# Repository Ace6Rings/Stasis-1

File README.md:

# OVERVIEW

The Reshular Robot Arm is a 6 DOF robotic arm. It is operated over bluetooth so it can be operated remotely.
5 stepper motors, using the TMC2209 driver, and 1 servo motor is used to make this huge robotic arm.

# Purpose

I made this because I've always been fascinated on how to use technology to make an impact on the physical world. 
I've seen small robotic arms powered with servo motors. But I noticed that scaling it up in size changes the materials I need 
and introduces (newish) problems like insufficient torque when using a servo motor. These robotic arms are also shorter ranged and can only hold
very light and small items. Thats why I built this robotic arm. I can lift items that are impossible for small robotic arms like a big book. 
The most important thing is that I became way better at eda since this is my first project that uses a smd PCB.

# Schematic

There are 5 tmc 2209 motor drivers. They are almost identical. Only their gpio assignments to dir and step changes and also their uart configuration.

So how did I configure it and how can you too?

The tmc2209 talks to the esp32 via UART. But four tmc 2209s share one uart line. Wait, there's 5 tmcs, not 4! How could that be?
Well, the ID for uart is dictated by the whether your ms1 and ms2 are pulled high or low. Since there are 2 states and 2 pins, 2^2 is 4. So you get 4 combinations.
To account for the 5th tmc 2209, I just used another set of gpios.

The ms1 and ms2 pins also happen to control microstepping, and thats pretty important if you have something like an EV or a robot arm like this. So I put the finer microstepping onto parts that actually matter, such as the elbow joint. You can find further details via the datasheet for the TMC2209 and the exact configuration in the PCB file that I have.
# PCB

Now lets get into the PCB.
The specs of the PCB isn't anything special. It is a 2 layer pcb, and thats exactly why this is good. It's theoretically not gonna perform as well as a four layer board (well not really because this is a 2 layer board thing). But since its only 2 layers, the cost decreases significantly. There are two layers of electrical protection. The first one is the NCP1117 (well not really? but if it dies the circuit becomes open so I guess it is protection), and the second one is the TVS diode. The TVS diode is a component that protects your circuit when the voltage/current reaches a certain threshold. For something like a robot arm, you will defininately one that.
# Model
The purpose of the model is not to make it look good but to make it as light as possible to test in real life. 
It features 6 degrees of freedom, which could move (almost) ny item in any way you could think of.

The base has an hexagonal pattern which maximizes strength, aesthetics, and filament efficiency.
# Motor joints

Well, how does each joint work? Its actually quite simple. You can tell by the picture that the stepper motors are directly attached to each joint, so no special pullys or anything! This saves complexity and cost. For the gripper, its a little different.

The central gear meshes with the two side parts. When it spins, the two grippers come together and, well, grips. Spinning it the opposite way retracts it. You can try it out in this link.
https://cad.onshape.com/documents/dfb7d85a38278a669fcebbb5/w/2d92252d034fc83197e6695c/e/ec9dc79179103d4b89a939a4?renderMode=0&uiState=6a322868ee269b265a1ceec7

As you can see, the motor is directly attached.

# Testing

N/A (will include after getting parts)

# Bill of Materials

| Name                          | Purpose                            | Quantity | Total Cost (USD) | Link                                                                                                                                                                                         | Distributor |
|-------------------------------|------------------------------------|----------|------------------|----------------------------------------------------------------------------------------------------------------------------------------------------------------------------------------------|-------------|
| li ion batteries              | batteries to power my robot arm    | 1        | 25.98            | https://www.amazon.com/Mupoer-Rechargeable-Batteries-Integrated-Charging/dp/B0D4M581B3/ref=sr_1_15?sr=8-15                                                                                   | amazon      |
| ds3225                        | gripper motor                      | 1        | 16.99            | https://www.amazon.com/gp/product/B0CNTG877G/ref=ox_sc_act_title_1?smid=A1PKC2PUMNR8VD                                                                                                       | amazon      |
| HEAT SET INSERTS              | To assemble my robot arm           | 1        | 9.98             | https://www.amazon.com/M2-M2-5-M3-Threaded-Inserts/dp/B0FH4JQ3VB/ref=sr_1_4?sr=8-4                                                                                                           | amazon      |
| 175-TMC2209-LA-TCT-ND         | IC MTR DRV 4.75-28V QFN28          | 10       | 40.89            | https://www.digikey.com/en/products/detail/analog-devices-inc-maxim-integrated/TMC2209-LA-T/10232491                                                                                         | DIGIKEY     |
| NCP1117LPST33T3GOSCT-ND       | IC REG LINEAR 3.3V 1A SOT-223      | 10       | 2.62             | https://www.digikey.com/en/products/detail/onsemi/NCP1117LPST33T3G/1967376                                                                                                                   | DIGIKEY     |
| 296-50511-1-ND                | UNIDIR PRECISION SURGE DIODE       | 10       | 7.06             | https://www.digikey.com/en/products/detail/texas-instruments/TVS1400DRVR/11589096                                                                                                            | DIGIKEY     |
| 2073-USB4085-GF-ACT-ND        | CONN RCPT USB2.0 TYPE C 16+8POS    | 2        | 2.15             | https://www.digikey.com/en/products/detail/gct/USB4085-GF-A/9859704                                                                                                                          | DIGIKEY     |
| CKN10285CT-ND                 | SWITCH TACTILE SPST-NO 0.05A 32V   | 10       | 5.81             | https://www.digikey.com/en/products/detail/c-k/KMR241NG-ULC-LFS/2747141                                                                                                                      | DIGIKEY     |
| 490-10700-1-ND                | CAP CER 0.1UF 50V X7R 0402         | 50       | 0.81             | https://www.digikey.com/en/products/detail/murata-electronics/GRM155R71H104KE14D/4358653                                                                                                     | DIGIKEY     |
| 277-1722-ND                   | TERM BLK 3POS SIDE ENT 3.5MM PCB   | 1        | 2.10             | https://www.digikey.com/en/products/detail/phoenix-contact/1984620/950937                                                                                                                    | DIGIKEY     |
| 1276-1096-1-ND                | CAP CER 10UF 16V X5R 0805          | 10       | 0.54             | https://www.digikey.com/en/products/detail/samsung-electro-mechanics/CL21A106KOQNNNE/3886902                                                                                                 | DIGIKEY     |
| 273-KDV12DR100ETCT-ND         | RES 0.1 OHM 0.5% 1/2W 1206         | 25       | 3.00             | https://www.digikey.com/en/products/detail/ohmite/KDV12DR100ET/13691867                                                                                                                      | DIGIKEY     |
| 311-5.10KLRCT-ND              | RES 5.1K OHM 1% 1/16W 0402         | 25       | 0.37             | https://www.digikey.com/en/products/detail/yageo/RC0402FR-075K1L/726633                                                                                                                      | DIGIKEY     |
| 541-10.0KLCT-ND               | RES 10K OHM 1% 1/16W 0402          | 25       | 0.59             | https://www.digikey.com/en/products/detail/vishay-dale/CRCW040210K0FKED/1176095                                                                                                              | DIGIKEY     |
| 311-100KLRCT-ND               | RES 100K OHM 1% 1/16W 0402         | 25       | 0.37             | https://www.digikey.com/en/products/detail/yageo/RC0402FR-07100KL/726651                                                                                                                     | DIGIKEY     |
| 311-1.00KLRCT-ND              | RES 1K OHM 1% 1/16W 0402           | 25       | 0.37             | https://www.digikey.com/en/products/detail/yageo/RC0402FR-071KL/726544                                                                                                                       | DIGIKEY     |
| 277-1721-ND                   | TERM BLK 2POS SIDE ENT 3.5MM PCB   | 1        | 1.46             | https://www.digikey.com/en/products/detail/phoenix-contact/1984617/950934                                                                                                                    | DIGIKEY     |
| 490-4763-1-ND                 | CAP CER 0.022UF 50V X7R 0402       | 50       | 1.01             | https://www.digikey.com/en/products/detail/murata-electronics/GCM155R71H223KA55D/2756835                                                                                                     | DIGIKEY     |
| 277-1860-ND                   | TERM BLK 4POS SIDE ENT 3.5MM PCB   | 5        | 13.45            | https://www.digikey.com/en/products/detail/phoenix-contact/1984633/950950                                                                                                                    | DIGIKEY     |
| 1965-ESP32-S3-WROOM-1-N4CT-ND | RF TXRX MODULE BT PCB TRACE SMD    | 2        | 11.46            | https://www.digikey.com/en/products/detail/espressif-systems/ESP32-S3-WROOM-1-N4/16162639                                                                                                    | DIGIKEY     |
| JLCPCB                        | To put my components on            | 1        | 36.48            | https://trade.jlcpcb.com/checkout/payMethod?systemType=order_pcb&calType=PAY&batchNum=W2026042809527003&spm=Jlcpcb.Confirmorder.1001                                                         | jlcpcb      |
| NEMA 17 motor thin            | For the arms                       | 5        | 17.50            | https://www.alibaba.com/product-detail/Special-Offer-26mm-Length-NEMA-17_1601043669710.html?spm=a2700.prosearch.normal_offer.d_title.659167afAhymea&priceId=58dcbf79d3ef4e1099ae55c89d924238 | Alibaba     |
| M2-M5 assortment screws       | To screw pcb, battery holders, and | 1        | 12.38            | https://www.amazon.com/Countersunk-Assortment-Phillips-Machine-Washers/dp/B0F87JTJ6T/ref=sr_1_3?sr=8-3                                                                                       | Amazon      |
| mr105                         | bearings for high torque load      | 4        | 8.79             | https://www.amazon.com/MR105-2RS-Deep-Groove-Ball-Bearings/dp/B0DXZNSMJC/ref=sr_1_6?sr=8-6                                                                                                   | amazon      |

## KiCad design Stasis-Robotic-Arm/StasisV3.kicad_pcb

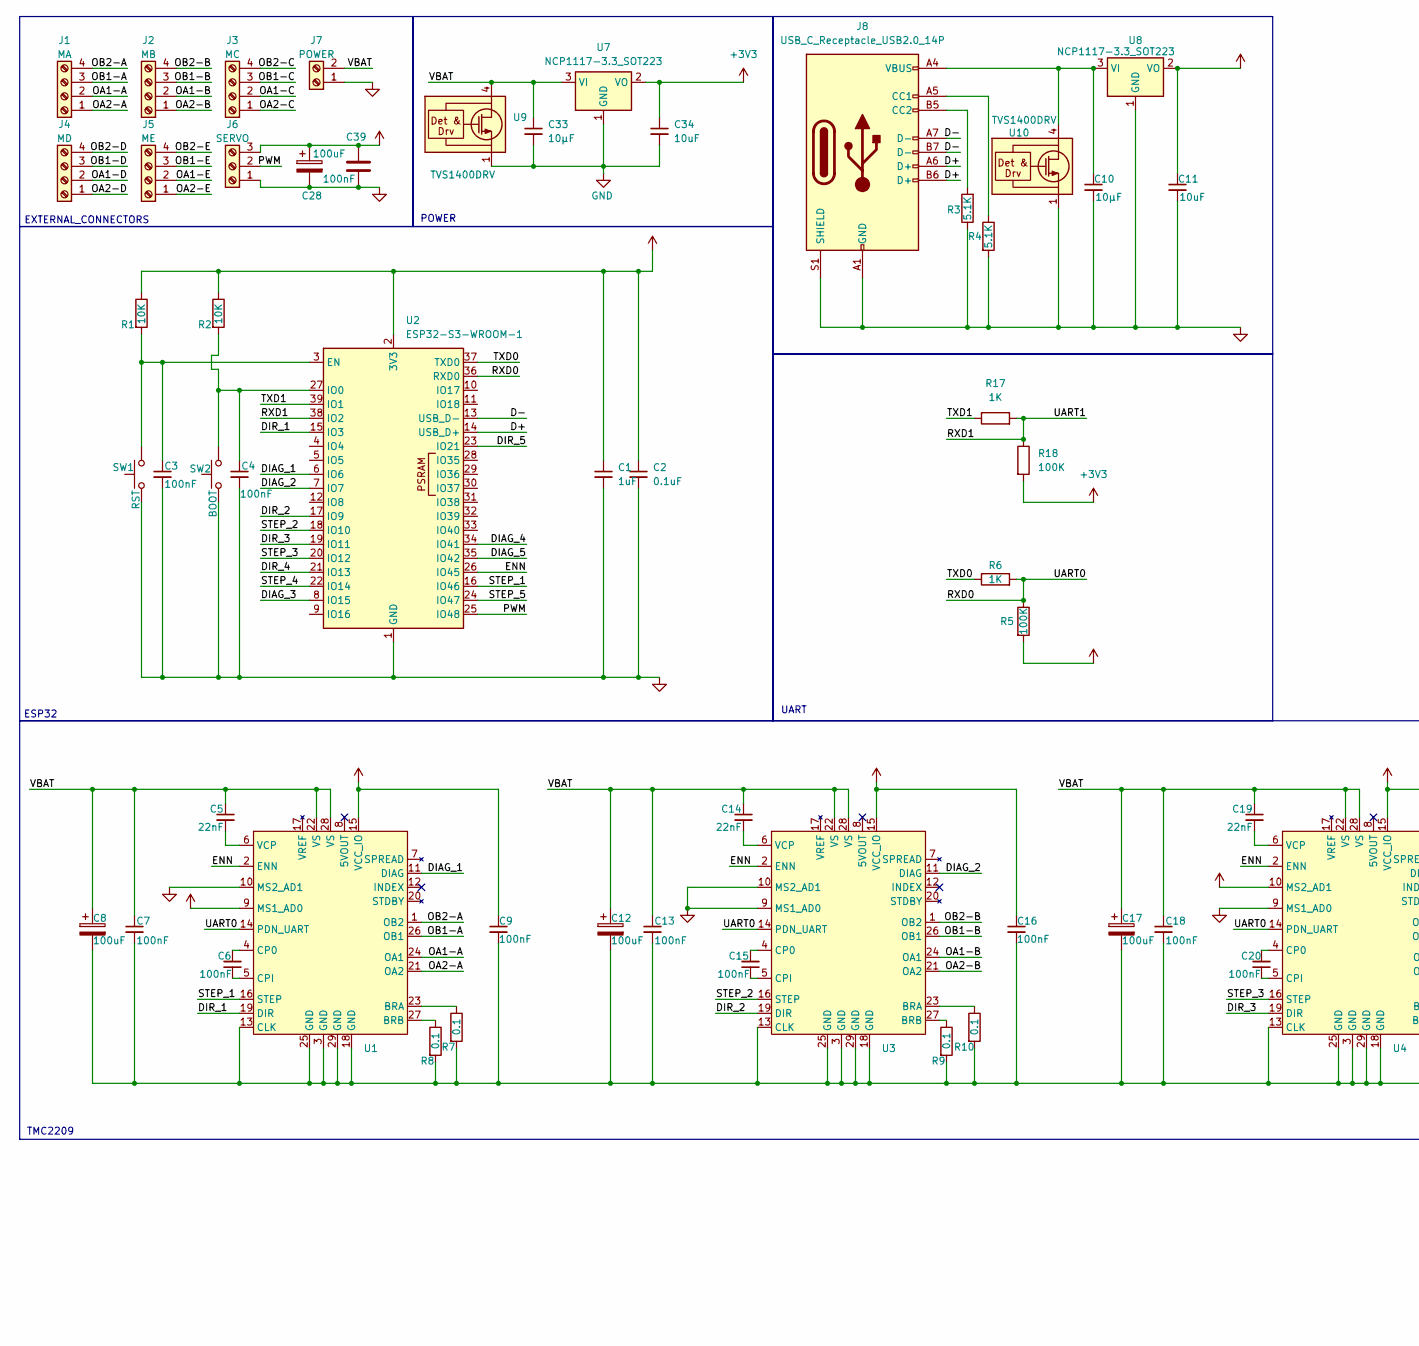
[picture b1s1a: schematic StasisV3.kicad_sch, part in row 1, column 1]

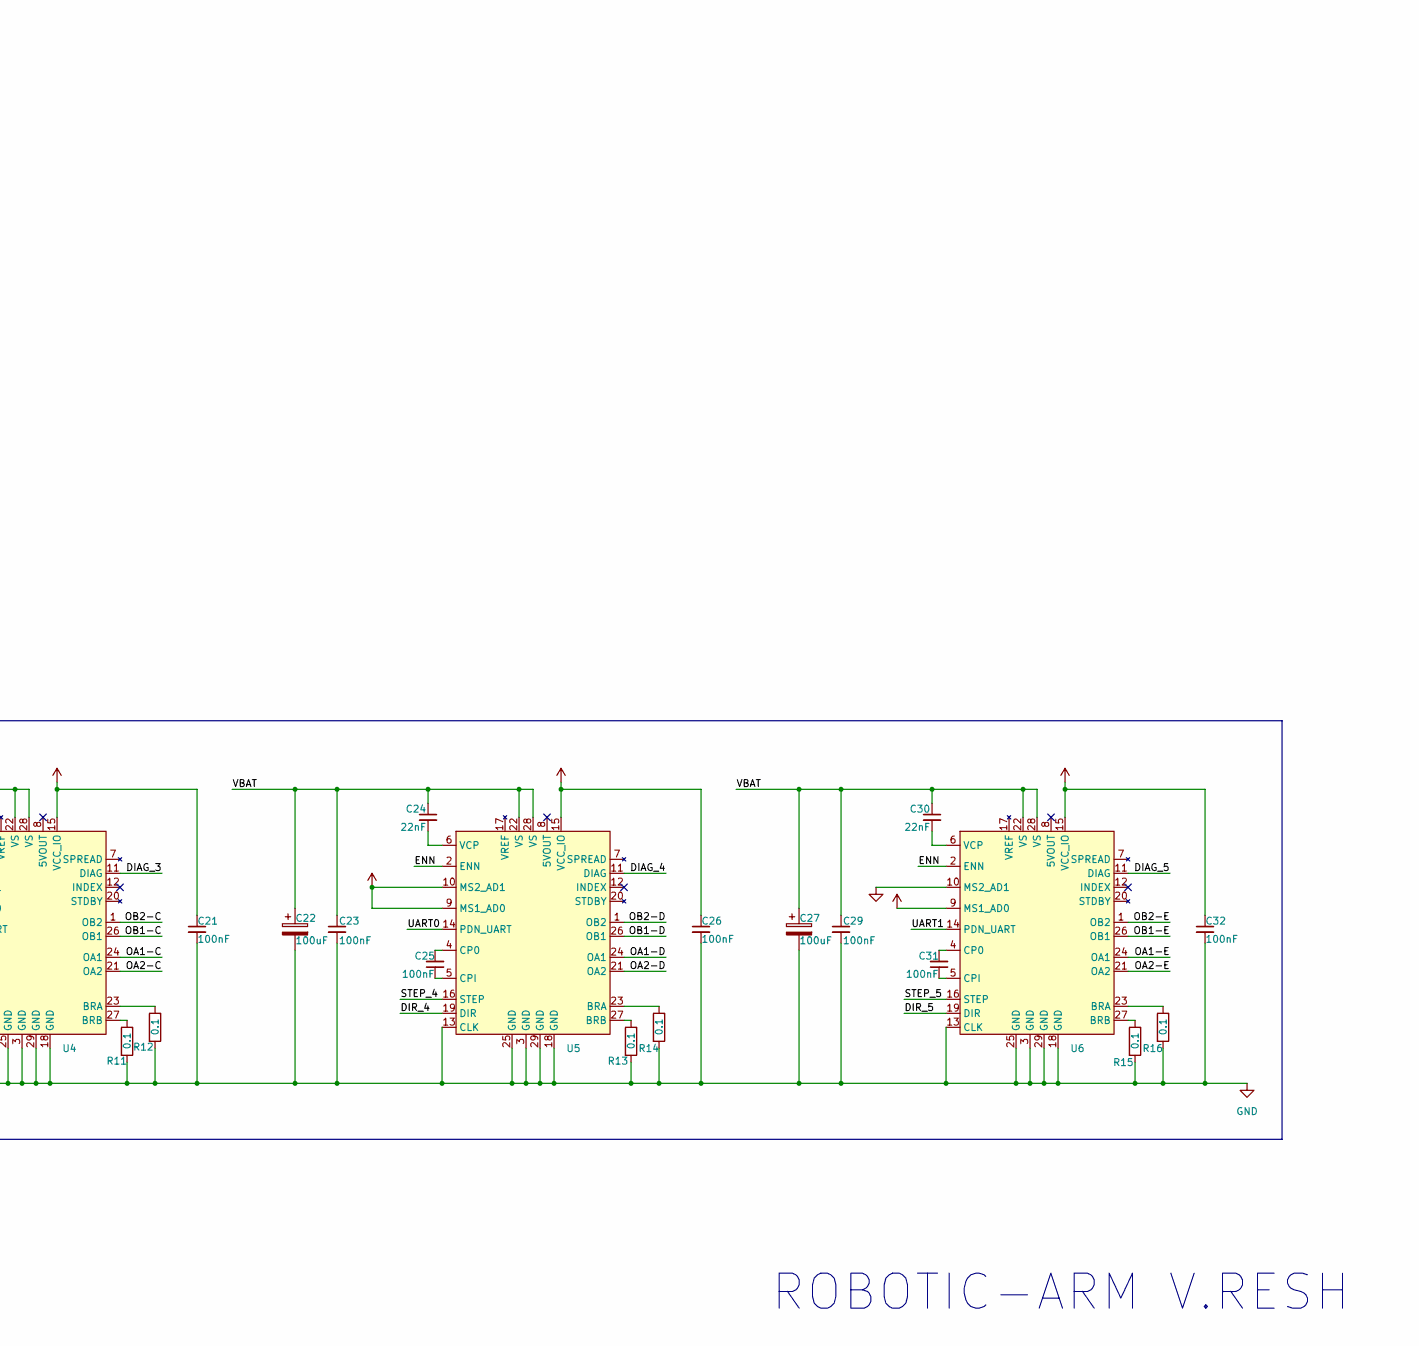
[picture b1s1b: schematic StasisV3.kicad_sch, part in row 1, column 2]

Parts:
C1: 1uF; C_0402_1005Metric
C2: 0.1uF; C_0402_1005Metric
C3, C4, C6, C7, C9, C13, C15, C16, C18, C20, C21, C23, C25, C26, C29, C31, C32, C39: 100nF; C_0402_1005Metric
C5, C14, C19, C24, C30: 22nF; C_0402_1005Metric
C8, C12, C17, C22, C27, C28: 100uF; CP_EIA-6032-28_Kemet-C
C10, C33: 10μF; C_0805_2012Metric
C11, C34: 10uF; C_0805_2012Metric
J1: MA; TerminalBlock_Phoenix_PT-1,5-4-3.5-H_1x04_P3.50mm_Horizontal
J2: MB; TerminalBlock_Phoenix_PT-1,5-4-3.5-H_1x04_P3.50mm_Horizontal
J3: MC; TerminalBlock_Phoenix_PT-1,5-4-3.5-H_1x04_P3.50mm_Horizontal
J4: MD; TerminalBlock_Phoenix_PT-1,5-4-3.5-H_1x04_P3.50mm_Horizontal
J5: ME; TerminalBlock_Phoenix_PT-1,5-4-3.5-H_1x04_P3.50mm_Horizontal
J6: SERVO; TerminalBlock_Phoenix_PT-1,5-3-3.5-H_1x03_P3.50mm_Horizontal
J7: POWER; TerminalBlock_Phoenix_PT-1,5-2-3.5-H_1x02_P3.50mm_Horizontal
J8: USB_C_Receptacle_USB2.0_14P; USB_C_Receptacle_GCT_USB4105-xx-A_16P_TopMnt_Horizontal
R1, R2: 10K; R_0402_1005Metric
R3, R4: 5.1K; R_0402_1005Metric
R5, R18: 100K; R_0402_1005Metric
R6, R17: 1K; R_0402_1005Metric
R7, R8, R9, R10, R11, R12, R13, R14, R15, R16: 0.1; R_1206_3216Metric
SW1: RST; SW_Push_1P1T_NO_CK_KMR2
SW2: BOOT; SW_Push_1P1T_NO_CK_KMR2
U1, U3, U4, U5, U6: tmc2209
U2: ESP32-S3-WROOM-1
U7, U8: NCP1117-3.3_SOT223; SOT-223-3_TabPin2
U9, U10: TVS1400DRV; WSON-6-1EP_2x2mm_P0.65mm_EP1x1.6mm

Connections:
+3V3: C1.1, C2.1, C9.1, C11.1, C16.1, C21.1, C26.1, C32.1, C34.1, R1.1, R2.1, R5.2, R18.2, U1.9 (MS1_AD0), U1.15 (VCC_IO), U2.2 (3V3), U3.15 (VCC_IO), U4.10 (MS2_AD1), U4.15 (VCC_IO), U5.9 (MS1_AD0), U5.10 (MS2_AD1), U5.15 (VCC_IO), U6.9 (MS1_AD0), U6.15 (VCC_IO), U7.2 (VO), U8.2 (VO)
/D+: J8.A6 (D+), J8.B6 (D+), U2.14 (USB_D+)
/D-: J8.A7 (D-), J8.B7 (D-), U2.13 (USB_D-)
/DIAG_1: U1.11 (DIAG), U2.6 (IO6)
/DIAG_2: U2.7 (IO7), U3.11 (DIAG)
/DIAG_3: U2.8 (IO15), U4.11 (DIAG)
/DIAG_4: U2.34 (IO41), U5.11 (DIAG)
/DIAG_5: U2.35 (IO42), U6.11 (DIAG)
/DIR_1: U1.19 (DIR), U2.15 (IO3)
/DIR_2: U2.17 (IO9), U3.19 (DIR)
/DIR_3: U2.19 (IO11), U4.19 (DIR)
/DIR_4: U2.21 (IO13), U5.19 (DIR)
/DIR_5: U2.23 (IO21), U6.19 (DIR)
/ENN: U1.2 (ENN), U2.26 (IO45), U3.2 (ENN), U4.2 (ENN), U5.2 (ENN), U6.2 (ENN)
/OA1-A: J1.2, U1.24 (OA1)
/OA1-B: J2.2, U3.24 (OA1)
/OA1-C: J3.2, U4.24 (OA1)
/OA1-D: J4.2, U5.24 (OA1)
/OA1-E: J5.2, U6.24 (OA1)
/OA2-A: J1.1, U1.21 (OA2)
/OA2-B: J2.1, U3.21 (OA2)
/OA2-C: J3.1, U4.21 (OA2)
/OA2-D: J4.1, U5.21 (OA2)
/OA2-E: J5.1, U6.21 (OA2)
/OB1-A: J1.3, U1.26 (OB1)
/OB1-B: J2.3, U3.26 (OB1)
/OB1-C: J3.3, U4.26 (OB1)
/OB1-D: J4.3, U5.26 (OB1)
/OB1-E: J5.3, U6.26 (OB1)
/OB2-A: J1.4, U1.1 (OB2)
/OB2-B: J2.4, U3.1 (OB2)
/OB2-C: J3.4, U4.1 (OB2)
/OB2-D: J4.4, U5.1 (OB2)
/OB2-E: J5.4, U6.1 (OB2)
/PWM: J6.2, U2.25 (IO48)
/RXD0: R5.1, R6.2, U1.14 (PDN_UART), U2.36 (RXD0), U3.14 (PDN_UART), U4.14 (PDN_UART), U5.14 (PDN_UART)
/RXD1: R17.2, R18.1, U2.38 (IO2), U6.14 (PDN_UART)
/STEP_1: U1.16 (STEP), U2.16 (IO46)
/STEP_2: U2.18 (IO10), U3.16 (STEP)
/STEP_3: U2.20 (IO12), U4.16 (STEP)
/STEP_4: U2.22 (IO14), U5.16 (STEP)
/STEP_5: U2.24 (IO47), U6.16 (STEP)
/TXD0: R6.1, U2.37 (TXD0)
/TXD1: R17.1, U2.39 (IO1)
unnamed: J8.A5 (CC1), R4.1
unnamed: J8.B5 (CC2), R3.2
unnamed: R7.1, U1.23 (BRA)
unnamed: R8.1, U1.27 (BRB)
unnamed: C6.2, U1.4 (CP0)
unnamed: C6.1, U1.5 (CPI)
unnamed: C5.2, U1.6 (VCP)
unnamed: R10.1, U3.23 (BRA)
unnamed: R9.1, U3.27 (BRB)
unnamed: C15.2, U3.4 (CP0)
unnamed: C15.1, U3.5 (CPI)
unnamed: C14.2, U3.6 (VCP)
unnamed: R12.1, U4.23 (BRA)
unnamed: R11.1, U4.27 (BRB)
unnamed: C20.2, U4.4 (CP0)
unnamed: C20.1, U4.5 (CPI)
unnamed: C19.2, U4.6 (VCP)
unnamed: R14.1, U5.23 (BRA)
unnamed: R13.1, U5.27 (BRB)
unnamed: C25.2, U5.4 (CP0)
unnamed: C25.1, U5.5 (CPI)
unnamed: C24.2, U5.6 (VCP)
unnamed: R16.1, U6.23 (BRA)
unnamed: R15.1, U6.27 (BRB)
unnamed: C31.2, U6.4 (CP0)
unnamed: C31.1, U6.5 (CPI)
unnamed: C30.2, U6.6 (VCP)
unnamed: C10.1, J8.A4 (VBUS), J8.A9 (VBUS), J8.B4 (VBUS), J8.B9 (VBUS), U8.3 (VI), U10.4 (IN), U10.5 (IN), U10.6 (IN)
VBAT: C5.1, C7.1, C8.1, C12.1, C13.1, C14.1, C17.1, C18.1, C19.1, C22.1, C23.1, C24.1, C27.1, C28.1, C29.1, C30.1, C33.1, C39.2, J6.3, J7.2, U1.22 (VS), U1.28 (VS), U3.22 (VS), U3.28 (VS), U4.22 (VS), U4.28 (VS), U5.22 (VS), U5.28 (VS), U6.22 (VS), U6.28 (VS), U7.3 (VI), U9.4 (IN), U9.5 (IN), U9.6 (IN)

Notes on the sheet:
TMC2209
POWER
UART
ESP32
EXTERNAL_CONNECTORS
ROBOTIC-ARM V.RESH

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
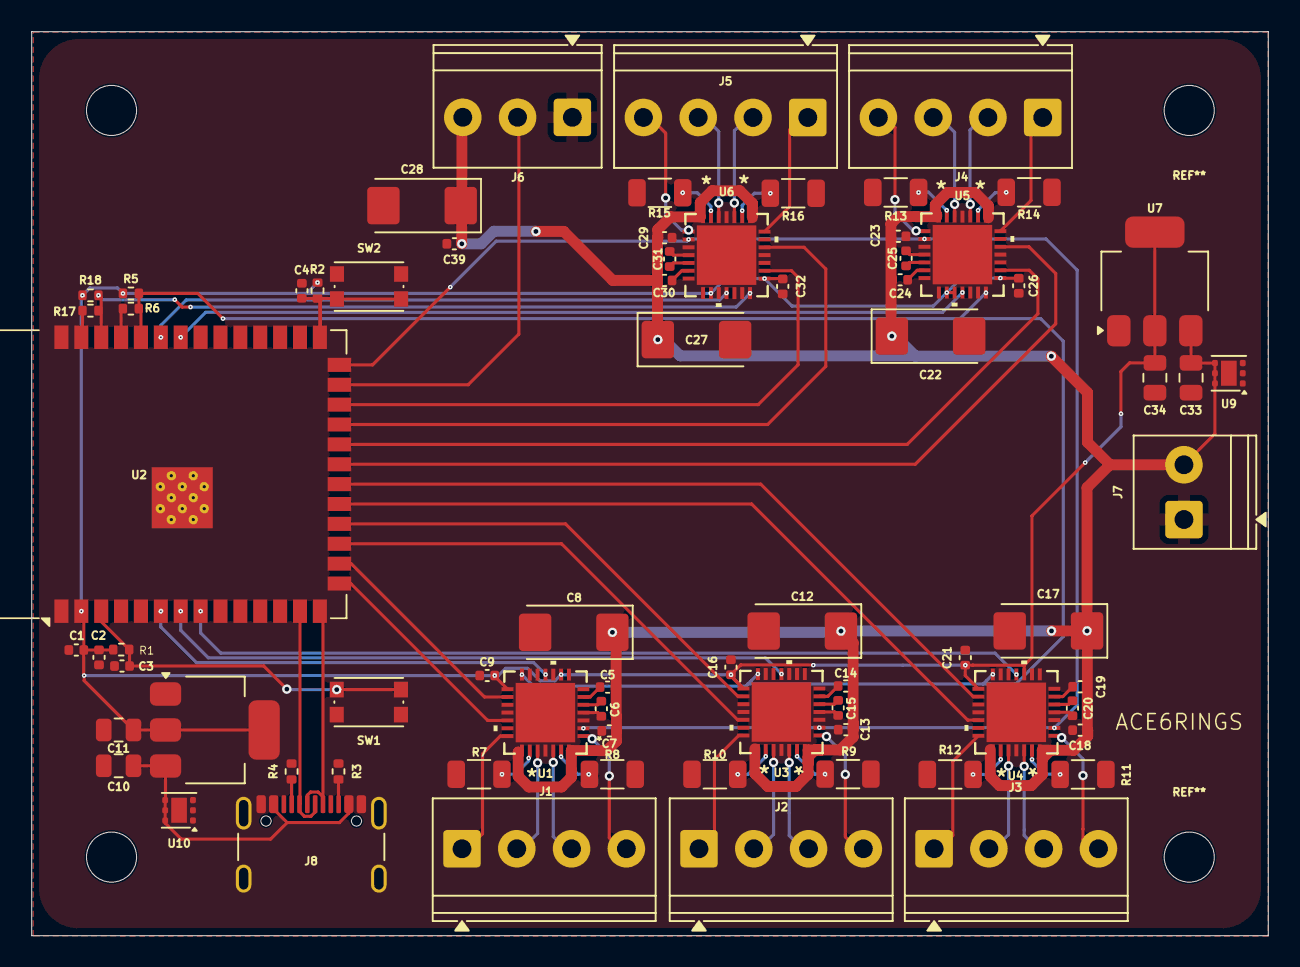
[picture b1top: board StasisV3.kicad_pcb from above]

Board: 2 copper layers, 79.0 x 57.8 mm, 73 parts (0 on the bottom side), 76 nets.

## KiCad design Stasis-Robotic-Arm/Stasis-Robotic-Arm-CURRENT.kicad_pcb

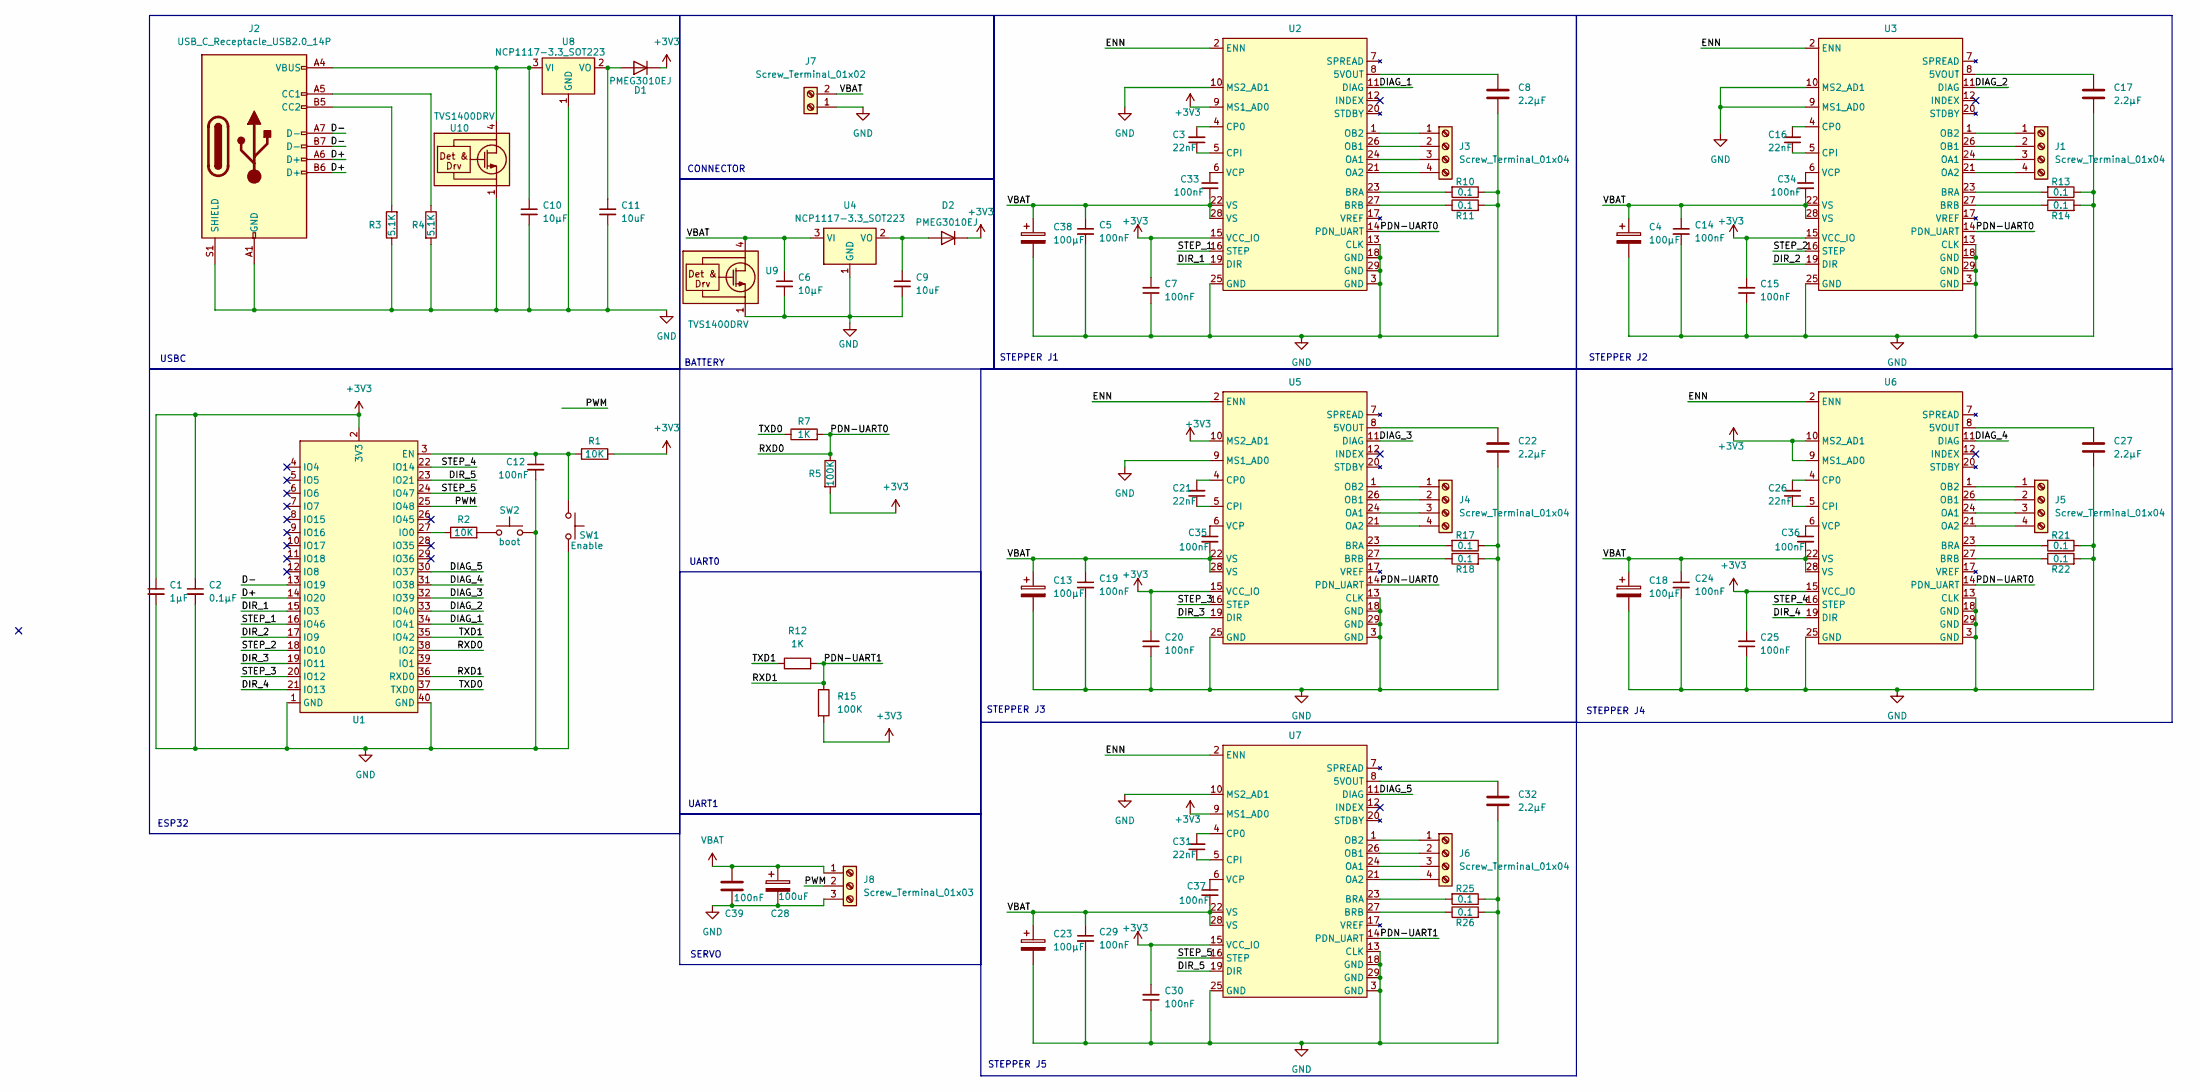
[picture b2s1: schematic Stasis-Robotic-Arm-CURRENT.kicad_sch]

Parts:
C1: 1μF; C_0402_1005Metric
C2: 0.1μF; C_0402_1005Metric
C3, C16, C21, C26, C31: 22nF; C_0402_1005Metric
C4, C13, C18, C23, C38: 100μF; CP_EIA-6032-28_Kemet-C
C5, C7, C12, C14, C15, C19, C20, C24, C25, C29, C30, C33, C34, C35, C36, C37, C39: 100nF; C_0402_1005Metric
C6, C10: 10μF; C_0805_2012Metric
C8, C17, C22, C27, C32: 2.2μF; C_0603_1608Metric
C9, C11: 10uF; C_0805_2012Metric
C28: 100uF; CP_EIA-6032-28_Kemet-C
D1, D2: PMEG3010EJ; D_SOD-123
J1, J3, J4, J5, J6: Screw_Terminal_01x04; PhoenixContact_GMSTBVA_2,5_4-G-7,62_1x04_P7.62mm_Vertical
J2: USB_C_Receptacle_USB2.0_14P; USB_C_Receptacle_GCT_USB4105-xx-A_16P_TopMnt_Horizontal
J7: Screw_Terminal_01x02; PhoenixContact_GMSTBVA_2,5_2-G-7,62_1x02_P7.62mm_Vertical
J8: Screw_Terminal_01x03; PhoenixContact_GMSTBVA_2,5_3-G-7,62_1x03_P7.62mm_Vertical
R1, R2: 10K; R_0402_1005Metric
R3, R4: 5.1K; R_0402_1005Metric
R5, R15: 100K; R_0402_1005Metric
R7, R12: 1K; R_0402_1005Metric
R10, R11, R13, R14, R17, R18, R21, R22, R25, R26: 0.1; R_1206_3216Metric
SW1: Enable; SW_Push_1P1T_NO_CK_KMR2
SW2: boot; SW_Push_1P1T_NO_CK_KMR2
U1: ESP32-S3-WROOM-1
U2, U3, U5, U6, U7: tmc2209
U4, U8: NCP1117-3.3_SOT223; SOT-223-3_TabPin2
U9, U10: TVS1400DRV; WSON-6-1EP_2x2mm_P0.65mm_EP1x1.6mm

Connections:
+3V3: C1.1, C2.1, C7.2, C15.2, C20.2, C25.2, C30.2, D1.1 (K), D2.1 (K), R1.2, R5.2, R15.2, U1.2 (3V3), U2.9 (MS1_AD0), U2.15 (VCC_IO), U3.15 (VCC_IO), U5.10 (MS2_AD1), U5.15 (VCC_IO), U6.9 (MS1_AD0), U6.10 (MS2_AD1), U6.15 (VCC_IO), U7.9 (MS1_AD0), U7.15 (VCC_IO)
/D+: J2.A6 (D+), J2.B6 (D+), U1.14 (IO20)
/D-: J2.A7 (D-), J2.B7 (D-), U1.13 (IO19)
/DIAG_1: U1.34 (IO41), U2.11 (DIAG)
/DIAG_2: U1.33 (IO40), U3.11 (DIAG)
/DIAG_3: U1.32 (IO39), U5.11 (DIAG)
/DIAG_4: U1.31 (IO38), U6.11 (DIAG)
/DIAG_5: U1.30 (IO37), U7.11 (DIAG)
/DIR_1: U1.15 (IO3), U2.19 (DIR)
/DIR_2: U1.17 (IO9), U3.19 (DIR)
/DIR_3: U1.19 (IO11), U5.19 (DIR)
/DIR_4: U1.21 (IO13), U6.19 (DIR)
/DIR_5: U1.23 (IO21), U7.19 (DIR)
/ENN: U2.2 (ENN), U3.2 (ENN), U5.2 (ENN), U6.2 (ENN), U7.2 (ENN)
/PDN-UART0: R5.1, R7.2, U1.38 (IO2), U2.14 (PDN_UART), U3.14 (PDN_UART), U5.14 (PDN_UART), U6.14 (PDN_UART)
/PDN-UART1: R12.2, R15.1, U1.36 (RXD0), U7.14 (PDN_UART)
/PWM: J8.2, U1.25 (IO48)
/STEP_1: U1.16 (IO46), U2.16 (STEP)
/STEP_2: U1.18 (IO10), U3.16 (STEP)
/STEP_3: U1.20 (IO12), U5.16 (STEP)
/STEP_4: U1.22 (IO14), U6.16 (STEP)
/STEP_5: U1.24 (IO47), U7.16 (STEP)
/TXD0: R7.1, U1.37 (TXD0)
/TXD1: R12.1, U1.35 (IO42)
GND: C1.2, C2.2, C4.2, C5.2, C6.2, C7.1, C8.2, C9.2, C10.2, C11.2, C12.2, C13.2, C14.2, C15.1, C17.2, C18.2, C19.2, C20.1, C22.2, C23.2, C24.2, C25.1, C27.2, C28.2, C29.2, C30.1, C32.2, C38.2, C39.2, J2.A1 (GND), J2.A12 (GND), J2.B1 (GND), J2.B12 (GND), J2.S1 (SHIELD), J7.1, J8.3, R3.1, R4.2, R10.1, R11.2, R13.1, R14.2, R17.1, R18.2, R21.1, R22.2, R25.1, R26.2, SW1.1, SW2.2, U1.1 (GND), U1.40 (GND), U2.3 (GND), U2.10 (MS2_AD1), U2.13 (CLK), U2.18 (GND), U2.25 (GND), U2.29 (GND), U3.3 (GND), U3.9 (MS1_AD0), U3.10 (MS2_AD1), U3.13 (CLK), U3.18 (GND), U3.25 (GND), U3.29 (GND), U4.1 (GND), U5.3 (GND), U5.9 (MS1_AD0), U5.13 (CLK), U5.18 (GND), U5.25 (GND), U5.29 (GND), U6.3 (GND), U6.13 (CLK), U6.18 (GND), U6.25 (GND), U6.29 (GND), U7.3 (GND), U7.10 (MS2_AD1), U7.13 (CLK), U7.18 (GND), U7.25 (GND), U7.29 (GND), U8.1 (GND), U9.1 (GND), U9.2 (GND), U9.3 (GND), U9.7 (GND), U10.1 (GND), U10.2 (GND), U10.3 (GND), U10.7 (GND)
unnamed: C11.1, D1.2 (A), U8.2 (VO)
unnamed: C9.1, D2.2 (A), U4.2 (VO)
unnamed: J1.1, U3.1 (OB2)
unnamed: J1.2, U3.26 (OB1)
unnamed: J1.3, U3.24 (OA1)
unnamed: J1.4, U3.21 (OA2)
unnamed: J2.A5 (CC1), R4.1
unnamed: J2.B5 (CC2), R3.2
unnamed: J3.1, U2.1 (OB2)
unnamed: J3.2, U2.26 (OB1)
unnamed: J3.3, U2.24 (OA1)
unnamed: J3.4, U2.21 (OA2)
unnamed: J4.1, U5.1 (OB2)
unnamed: J4.2, U5.26 (OB1)
unnamed: J4.3, U5.24 (OA1)
unnamed: J4.4, U5.21 (OA2)
unnamed: J5.1, U6.1 (OB2)
unnamed: J5.2, U6.26 (OB1)
unnamed: J5.3, U6.24 (OA1)
unnamed: J5.4, U6.21 (OA2)
unnamed: J6.1, U7.1 (OB2)
unnamed: J6.2, U7.26 (OB1)
unnamed: J6.3, U7.24 (OA1)
unnamed: J6.4, U7.21 (OA2)
unnamed: R2.2, SW2.1
unnamed: C12.1, R1.1, SW1.2, U1.3 (EN)
unnamed: R2.1, U1.27 (IO0)
unnamed: C8.1, U2.8 (5VOUT)
unnamed: R10.2, U2.23 (BRA)
unnamed: R11.1, U2.27 (BRB)
unnamed: C3.2, U2.4 (CP0)
unnamed: C3.1, U2.5 (CPI)
unnamed: C33.1, U2.6 (VCP)
unnamed: C17.1, U3.8 (5VOUT)
unnamed: R13.2, U3.23 (BRA)
unnamed: R14.1, U3.27 (BRB)
unnamed: C16.2, U3.4 (CP0)
unnamed: C16.1, U3.5 (CPI)
unnamed: C34.1, U3.6 (VCP)
unnamed: C22.1, U5.8 (5VOUT)
unnamed: R17.2, U5.23 (BRA)
unnamed: R18.1, U5.27 (BRB)
unnamed: C21.2, U5.4 (CP0)
unnamed: C21.1, U5.5 (CPI)
unnamed: C35.1, U5.6 (VCP)
unnamed: C27.1, U6.8 (5VOUT)
unnamed: R21.2, U6.23 (BRA)
unnamed: R22.1, U6.27 (BRB)
unnamed: C26.2, U6.4 (CP0)
unnamed: C26.1, U6.5 (CPI)
unnamed: C36.1, U6.6 (VCP)
unnamed: C32.1, U7.8 (5VOUT)
unnamed: R25.2, U7.23 (BRA)
unnamed: R26.1, U7.27 (BRB)
unnamed: C31.2, U7.4 (CP0)
unnamed: C31.1, U7.5 (CPI)
unnamed: C37.1, U7.6 (VCP)
unnamed: C10.1, J2.A4 (VBUS), J2.A9 (VBUS), J2.B4 (VBUS), J2.B9 (VBUS), U8.3 (VI), U10.4 (IN), U10.5 (IN), U10.6 (IN)
VBAT: C4.1, C5.1, C6.1, C13.1, C14.1, C18.1, C19.1, C23.1, C24.1, C28.1, C29.1, C33.2, C34.2, C35.2, C36.2, C37.2, C38.1, C39.1, J7.2, J8.1, U2.22 (VS), U2.28 (VS), U3.22 (VS), U3.28 (VS), U4.3 (VI), U5.22 (VS), U5.28 (VS), U6.22 (VS), U6.28 (VS), U7.22 (VS), U7.28 (VS), U9.4 (IN), U9.5 (IN), U9.6 (IN)

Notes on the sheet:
STEPPER J2
STEPPER J5
BATTERY
SERVO
USBC
STEPPER J1
ESP32
STEPPER J3
STEPPER J4
UART1
CONNECTOR
UART0

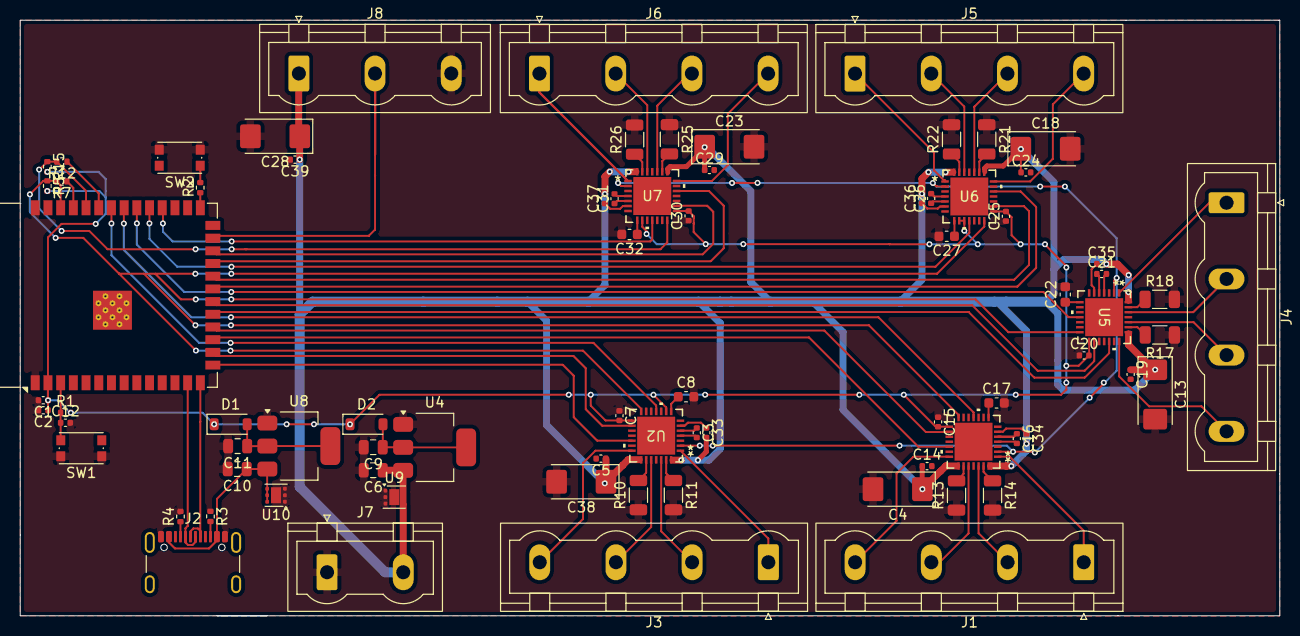
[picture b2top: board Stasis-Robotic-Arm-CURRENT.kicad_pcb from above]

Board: 2 copper layers, 125.9 x 59.6 mm, 79 parts (0 on the bottom side), 84 nets.

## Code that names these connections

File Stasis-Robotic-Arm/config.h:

#define MY_SSID       "YOUR_SSID"
#define MY_PASS       "YOUR_PASSWORD"
#ifndef CONFIG_H
#define CONFIG_H
#define OTA_HOSTNAME  "stasis-arm"
 
// Bus 1: GPIO1 (TX) / GPIO2 (RX) — drivers 1-4 (addresses 0-3)
// Bus 2: GPIO17 (TX) / GPIO18 (RX) — driver 5 (address 0)
#define TMC_BUS1_TX   1
#define TMC_BUS1_RX   2
#define TMC_BUS2_TX   17
#define TMC_BUS2_RX   18
#define TMC_BAUD      115200
#define R_SENSE       0.10f
 
#define STEP_1  5
#define DIR_1   4
#define STEP_2  6
#define DIR_2   7
#define STEP_3  9
#define DIR_3   10
#define STEP_4  11
#define DIR_4   12
#define STEP_5  13
#define DIR_5   8
 
#define DIAG_1  21
#define DIAG_2  38
#define DIAG_3  39
#define DIAG_4  44
#define DIAG_5  43
 
#define SERVO_PIN  47
 
#define DEFAULT_CURRENT_MA   800
#define DEFAULT_MICROSTEPS   16
#define DEFAULT_SPEED        400
#define DEFAULT_ACCEL        800
#define SERVO_MIN_US   500
#define SERVO_MAX_US   2500
 
#define SERIAL_BUF_SIZE  128
#define NUM_JOINTS       5
 
#endif

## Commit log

2026-04-10 Add MIT License to the project
2026-04-11 Add files via upload
    Schematic
2026-04-29 Initialize README with project details and BOM
    Added project description, images, and bill of materials (BOM) for the robotic arm.
2026-05-17 Revise README with project overview and purpose
    Updated the overview and purpose sections, added details about the robotic arm's components and capabilities.
2026-05-17 Create 3D printer files
2026-05-17 Create y
2026-06-08 Update README with image and overview details
    Added an image and expanded the overview section.
